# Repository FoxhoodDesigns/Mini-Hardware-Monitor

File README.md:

# Mini-Hardware-Monitor
This Repository contains the Source/release files for the FHD Mini Hardware Monitor project. A miniature LibreHardwareMonitor based program intended for providing hardware info via Serial to external devices and Arduino projects.
Designed to be as small and simple as i could make it.

# Working:
The program is a tiny C# program that uses the LiberHardwareMonitor library DLL to retrieve various sensor values from the system, convert them into a set of bytes and then pushes them out a COM port.
To keep its footprint to a minimum the program lacks window, instead existing solely as a system tray icon.

It has a footprint of about 8 megabyte of ram and negligable CPU use.

# Protocol
The program sends out a packet of 7 bytes every second via serial.
It uses the standard UART settings as found on an arduino with a Baud rate of 115200.

* Byte 1-2: Static 0x03 & 0xF4 (Pre-amble)
* Byte 3: CPU use 
* Byte 4: RAM use
* Byte 5: GPU use
* Byte 6: CPU temp
* Byte 7: GPU temp

Value is stored in halves (0x01 = 0.5). e.g. a byte with as value 150 is either 75% or 75 degrees.

# Configuring for automatic startup
If your project is nice and and it got its own static com-port. You can configure the monitor program to automatically try to connect to a specific COM port on start.
To set this up you have to open the .Settings file within the folder with a text editor. There you will find a set of field for automatic connecting.

I went for this approach as the alternative would have the program create itself a local appdata folder and i rather avoid such clutter.

# CPU Temperature is 0?
CPU Temperature is the only value that requires Admin rights to run. If you want that value you will want to run as administrator

# My hardware isn't detected!!
The Librehardwaremonitor is subject to constant updates for new hardware and it is almost guaranteed that this project will often lag behind.
To fix it yourself you can go to the LibrehardwareMonitor github, download the latest version of the lib DLL file and replace the one that is bundled within this project.
This is often enough for the program to start detecting boards again. May take a few weeks if you got like a cutting edge new board

# License:
The LibreHardwareMonitor project is subject to the Mozilla Public License 2.0. Please observe their own github pages for specifics.
This program is Fully Open Source. Fork, copy, re-use bits however you please. It is nothing special honestly.

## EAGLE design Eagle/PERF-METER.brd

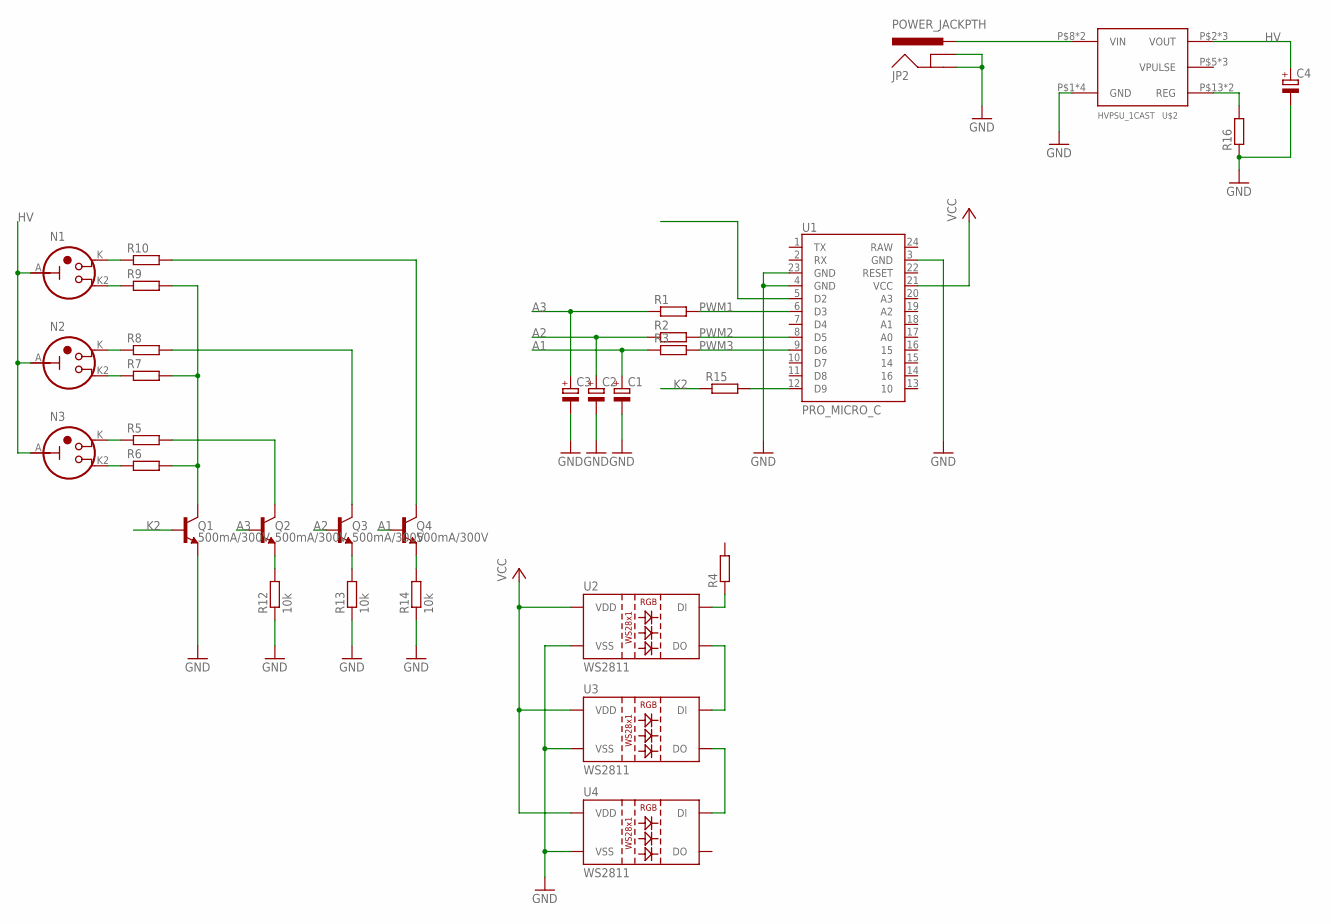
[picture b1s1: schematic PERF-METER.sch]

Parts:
C1, C2, C3, C4: CPOL-EUE2-4; E2-4
JP2: POWER_JACKPTH; POWER_JACK_PTH
N1, N2, N3: IN-13
Q1, Q2, Q3, Q4: 500mA/300V; SOT23-3
R1, R2, R3, R4, R15, R16: R-EU_R0805; R0805
R5, R6, R7, R8, R9, R10: R-EU_0207/7; 0207/7
R12, R13, R14: 10k; R0805
U1: PRO_MICRO_C
U2, U3, U4: WS2811; LED-TRICOLOR-5050-IC
U$2: HVPSU_1CAST; HVPSU_CASTELATED

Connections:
A1: C1.+, Q4.1 (B), R3.1
A2: C2.+, Q3.1 (B), R2.1
A3: C3.+, Q2.1 (B), R1.1
GND: C1.-, C2.-, C3.-, C4.-, JP2.GND, JP2.GNDBREAK, Q1.2 (E), R12.1, R13.1, R14.1, R16.1, U1.3 (GND), U1.4 (GND), U1.23 (GND), U2.6 (VSS), U3.6 (VSS), U4.6 (VSS), U$2.P$1 (GND), U$2.P$10 (GND), U$2.P$11 (GND), U$2.P$12 (GND)
HV: C4.+, N1.A, N2.A, N3.A, U$2.P$2 (VOUT), U$2.P$3 (VOUT), U$2.P$4 (VOUT)
K2: Q1.1 (B), R15.1
unnamed: R15.2, U1.12 (D9)
unnamed: R16.2, U$2.P$13 (REG), U$2.P$14 (REG)
unnamed: U2.1 (DO), U3.2 (DI)
unnamed: JP2.PWR, U$2.P$8 (VIN), U$2.P$9 (VIN)
unnamed: U3.1 (DO), U4.2 (DI)
unnamed: N1.K, R10.1
unnamed: N1.K2, R9.1
unnamed: R4.1, U2.2 (DI)
unnamed: N2.K, R8.1
unnamed: N2.K2, R7.1
unnamed: N3.K, R5.1
unnamed: N3.K2, R6.1
unnamed: Q1.3 (C), R6.2, R7.2, R9.2
unnamed: Q3.3 (C), R8.2
unnamed: Q2.3 (C), R5.2
unnamed: Q4.3 (C), R10.2
unnamed: Q2.2 (E), R12.2
unnamed: Q3.2 (E), R13.2
unnamed: Q4.2 (E), R14.2
PWM1: R1.2, U1.6 (D3)
PWM2: R2.2, U1.8 (D5)
PWM3: R3.2, U1.9 (D6)
VCC: U1.21 (VCC), U2.3 (VDD), U2.5 (VDD), U3.3 (VDD), U3.5 (VDD), U4.3 (VDD), U4.5 (VDD)

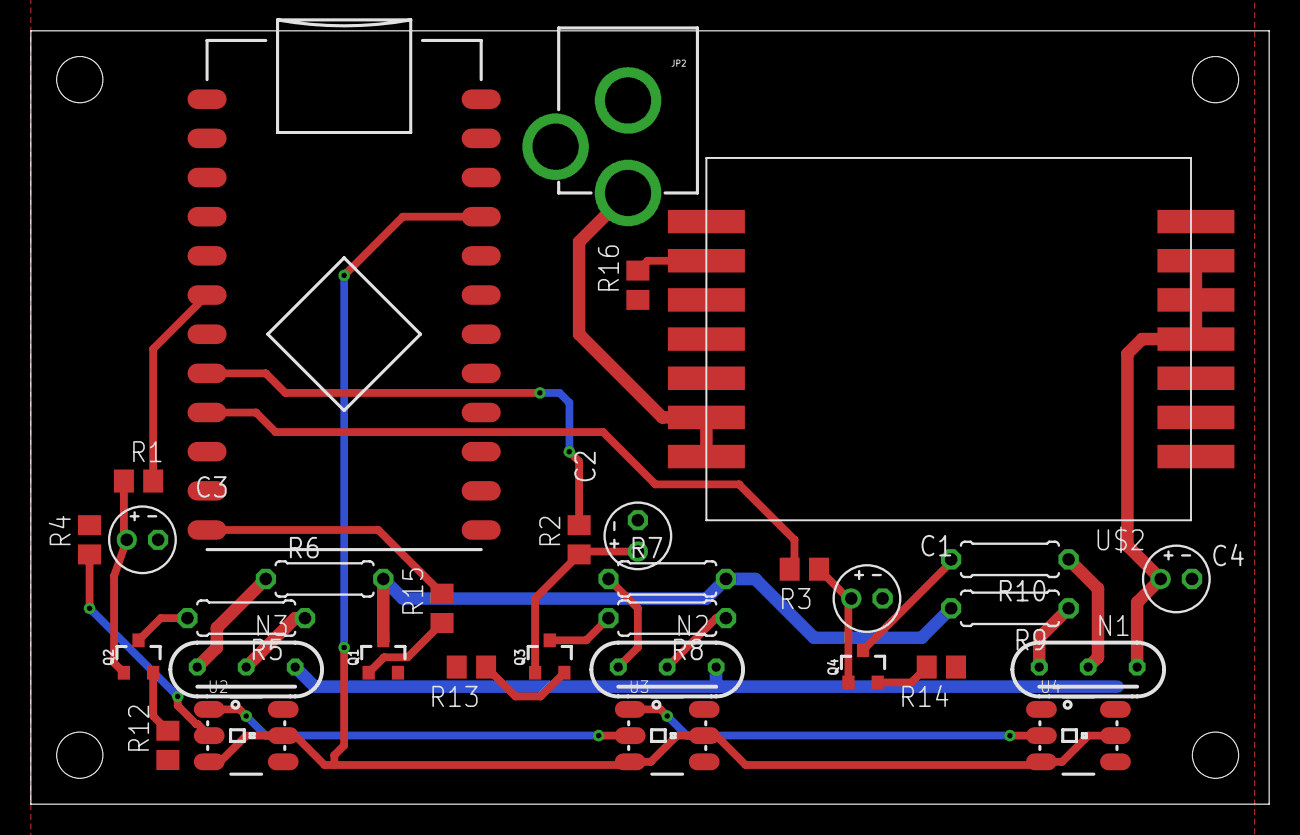
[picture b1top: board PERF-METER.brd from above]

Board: 2 copper layers, 80.3 x 50.2 mm, 32 parts (0 on the bottom side), 29 nets.

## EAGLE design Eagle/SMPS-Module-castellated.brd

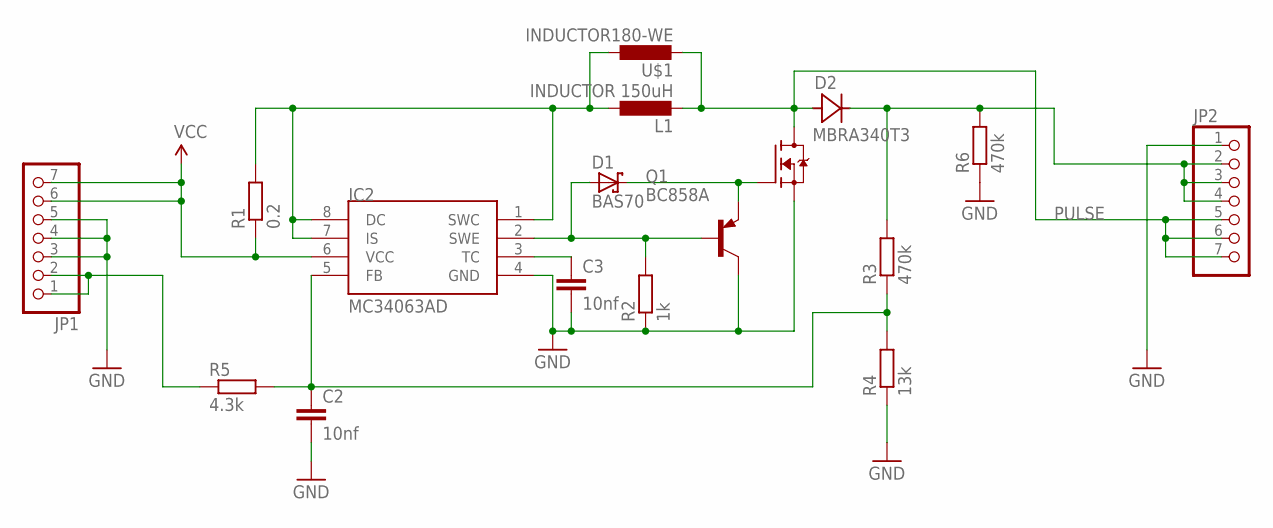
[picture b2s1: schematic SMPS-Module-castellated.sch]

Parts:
C2, C3: 10nf; C0805
D1: BAS70; SOT23
D2: MBRA340T3; SMA
IC2: MC34063AD; SOIC8
JP1, JP2: PINHD-1X7; 1X07
L1: INDUCTOR 150uH; SDR1806(BOURNS)
Q1: BC858A; SOT23-BEC
R1: 0.2; R2512
R2: 1k; R0805
R3, R6: 470k; R0805
R4: 13k; R0805
R5: 4.3k; R0805
U$1: INDUCTOR180-WE; WE180-744770218
U$2: POWER-NFETTDSON; PG-TDSON-8

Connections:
GND: C2.2, C3.2, IC2.4 (GND), JP1.3, JP1.4, JP1.5, JP2.1, Q1.C, R2.1, R4.1, R6.1, U$2.1 (S), U$2.2 (S), U$2.3 (S)
unnamed: JP1.1, JP1.2, R5.1
unnamed: D1.1 (A), IC2.2 (SWE), Q1.B, R2.2
unnamed: C3.1, IC2.3 (TC)
unnamed: C2.1, IC2.5 (FB), R3.1, R4.2, R5.2
unnamed: IC2.1 (SWC), IC2.7 (IS), IC2.8 (DC), L1.P$1 (1), R1.2, U$1.P$1 (1)
unnamed: D1.3 (C), Q1.E, U$2.4 (G)
unnamed: D2.C, JP2.2, JP2.3, JP2.4, R3.2, R6.2
PULSE: D2.A, JP2.5, JP2.6, JP2.7, L1.P$2 (2), U$1.P$2 (2), U$2.5 (D), U$2.6 (D), U$2.7 (D), U$2.8 (D), U$2.TH (D)
VCC: IC2.6 (VCC), JP1.6, JP1.7, R1.1

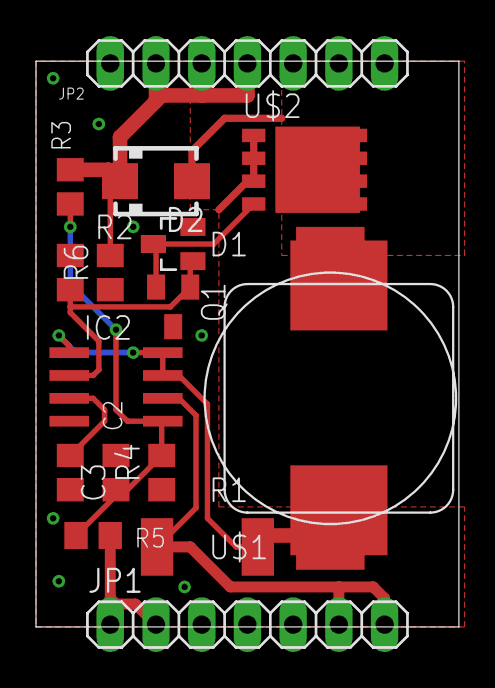
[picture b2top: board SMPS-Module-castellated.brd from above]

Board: 2 copper layers, 23.5 x 31.4 mm, 17 parts (0 on the bottom side), 10 nets.

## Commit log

2020-08-10 Initial upload Project files
2024-08-03 Upgrade to LibreHardwareMonitor
    Updated application to utilize LibreHardwareMonitorLib over the long deprecated OpenHardwareMonitorLib. To allow detection of newer hardware.
    Also implemented ability to use the settings file to set a COM port in advance for automatic start up.
2024-12-22 LHML update
    Updated LibreHardwareMonitorLib to latest version
2024-12-22 small example
    Quick Arduino example
2025-06-01 V0.5
    Major update. Or at least enough so it is working and can be used by people to have fun.
2025-06-01 Create RGB_Matrix_HWM.ino
    Added the RGB Matrix Example

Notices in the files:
parts and their libraries:
SparkFun-Boards: Licensing: Creative Commons ShareAlike 4.0 International - https://creativecommons.org/licenses/by-sa/4.0
